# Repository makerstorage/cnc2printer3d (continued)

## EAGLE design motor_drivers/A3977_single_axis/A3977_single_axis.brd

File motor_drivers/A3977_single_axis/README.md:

A3977 Single Stepper Motor Driver Board

For more details, check out the product pages at

http://makerstorage.com/index.php?id_product=16&controller=product

MakerStorage invests time and resources providing this open source design, please support MakerStorage and open-source hardware by purchasing products from MakerStorage!

Designed by MakerStorage LLC.

Creative Commons Attribution, Share-Alike license, check https://creativecommons.org/licenses/by-sa/3.0/ for more information All text above must be included in any redistribution

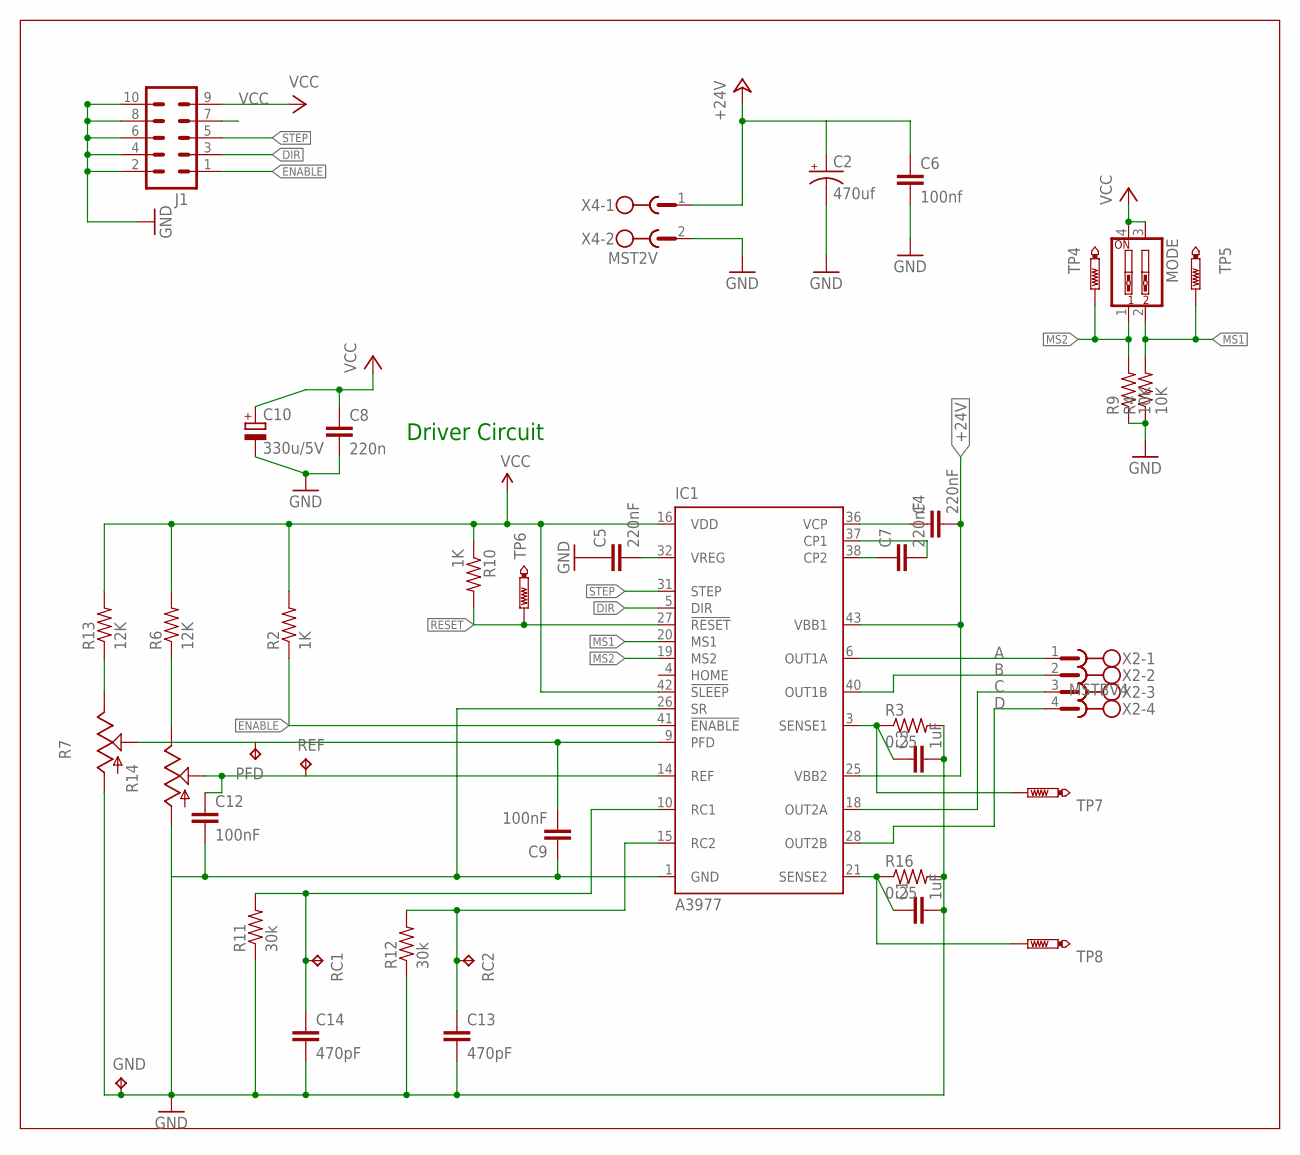
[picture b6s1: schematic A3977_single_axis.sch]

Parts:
C1, C3: 1uF; 0805
C2: 470uf; NIC_10X10.5_CAP
C4, C5, C7: 220nF; 0805
C6: 100nf; C1206
C8: 220n; C0805
C9, C12: 100nF; 0805
C10: 330u/5V; PANASONIC_F
C13, C14: 470pF; 0805
GND: TPPAD1-13; P1-13
IC1: A3977; PLCC44
J1: M05X2SHD; 2X5-SHROUDED
MODE: SW_DIP-2; EDG-02
PFD: TPPAD1-13; P1-13
R2, R10: 1K; 0805
R3, R16: 0.25; R2512
R4, R9: 10K; 0805
R6, R13: 12K; 0805
R7, R14: TRIM_US-CA6V; CA6V
R11, R12: 30k; 0805
RC1, RC2: TPPAD1-13; P1-13
REF: TPPAD1-13; P1-13
TP4, TP5, TP6, TP7, TP8: PTR1TP09R; TP09R
X2: MSTBV4
X4: MST2V; MSTBV2

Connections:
+24V: C2.+, C4.2, C6.1, IC1.25 (VBB2), IC1.43 (VBB1), X4.1
A: IC1.6 (OUT1A), X2.1
B: IC1.40 (OUT1B), X2.2
C: IC1.18 (OUT2A), X2.3
D: IC1.28 (OUT2B), X2.4
DIR: IC1.5 (DIR), J1.3
ENABLE: IC1.41 (!ENABLE), J1.1, R2.1
GND: C1.2, C2.-, C3.2, C5.1, C6.2, C8.2, C9.1, C10.-, C12.2, C13.2, C14.2, GND.TP, IC1.1 (GND), IC1.2 (GND), IC1.11 (GND), IC1.12 (GND), IC1.13 (GND), IC1.22 (GND), IC1.23 (GND), IC1.24 (GND), IC1.26 (SR), IC1.33 (GND), IC1.34 (GND), IC1.35 (GND), IC1.44 (GND), J1.2, J1.4, J1.6, J1.8, J1.10, R3.2, R4.1, R7.A, R9.1, R11.1, R12.1, R14.A, R16.2, X4.2
MS1: IC1.20 (MS1), MODE.2, R4.2, TP5.TP
MS2: IC1.19 (MS2), MODE.1, R9.2, TP4.TP
unnamed: C3.1, IC1.3 (SENSE1), R3.1, TP7.TP
unnamed: C1.1, IC1.21 (SENSE2), R16.1, TP8.TP
unnamed: C9.2, IC1.9 (PFD), PFD.TP, R7.S
unnamed: C14.1, IC1.10 (RC1), R11.2, RC1.TP
unnamed: C13.1, IC1.15 (RC2), R12.2, RC2.TP
unnamed: R6.1, R14.E
unnamed: C5.2, IC1.32 (VREG)
unnamed: R7.E, R13.1
unnamed: C7.1, IC1.38 (CP2)
unnamed: C12.1, IC1.14 (REF), R14.S, REF.TP
unnamed: C7.2, IC1.37 (CP1)
unnamed: C4.1, IC1.36 (VCP)
RESET: IC1.27 (!RESET), R10.2, TP6.TP
STEP: IC1.31 (STEP), J1.5
VCC: C8.1, C10.+, IC1.16 (VDD), IC1.42 (!SLEEP), J1.9, MODE.3, MODE.4, R2.2, R6.2, R10.1, R13.2

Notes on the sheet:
Driver Circuit

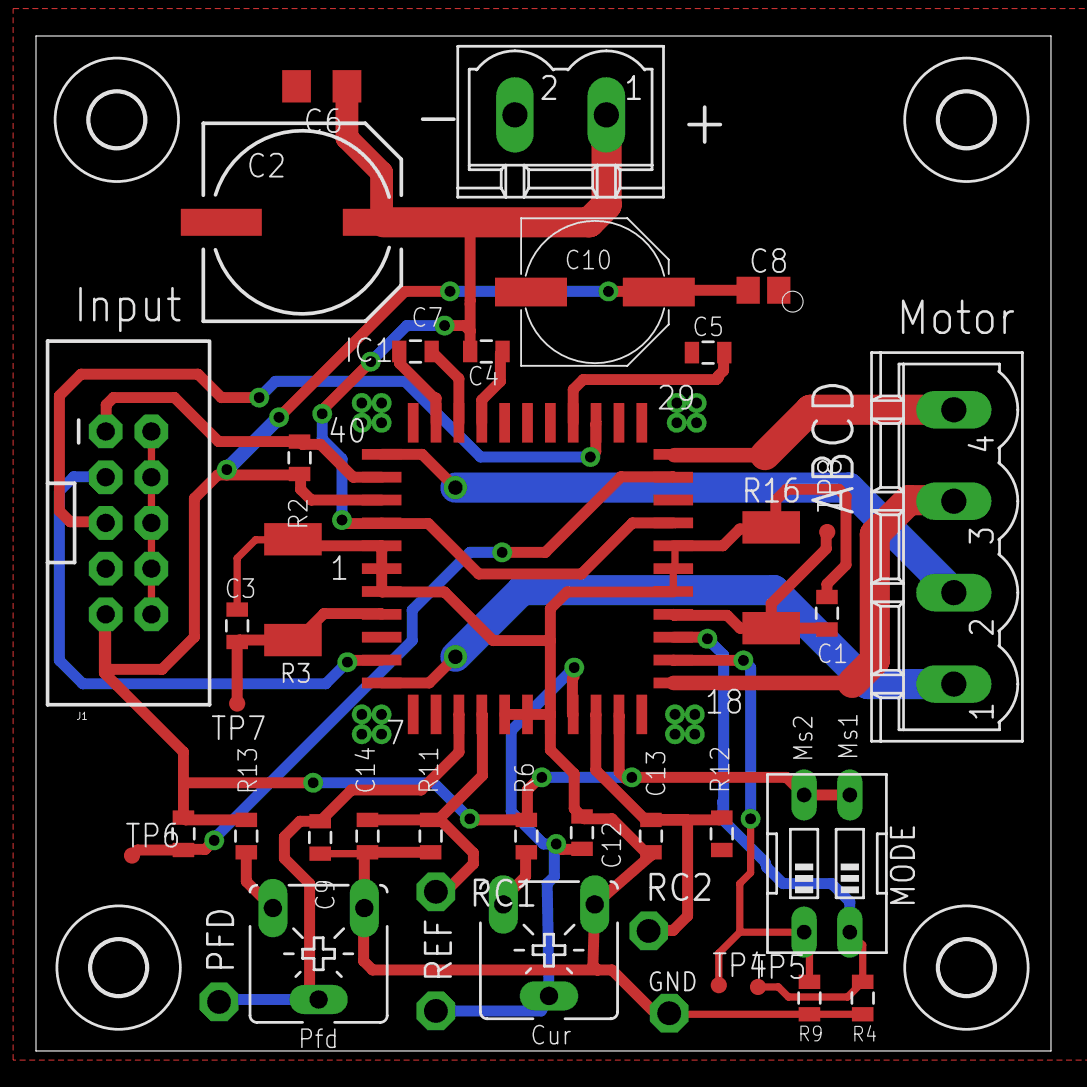
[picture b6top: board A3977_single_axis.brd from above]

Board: 2 copper layers, 56.4 x 56.4 mm, 44 parts (0 on the bottom side), 25 nets.

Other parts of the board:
U$1, U$2, U$3, U$4: 3,0

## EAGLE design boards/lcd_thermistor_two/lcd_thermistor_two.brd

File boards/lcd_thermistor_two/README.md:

LCD Thermistor Two Channel Extruder Controller (gecs2ts1)

For more details, check out the product pages at

https://cnc2printer3d.wordpress.com/gecs2ts1/

MakerStorage invests time and resources providing this open source design, please support MakerStorage and open-source hardware by purchasing products from MakerStorage!

Designed by MakerStorage LLC.

Creative Commons Attribution, Share-Alike license, check https://creativecommons.org/licenses/by-sa/3.0/ for more information All text above must be included in any redistribution

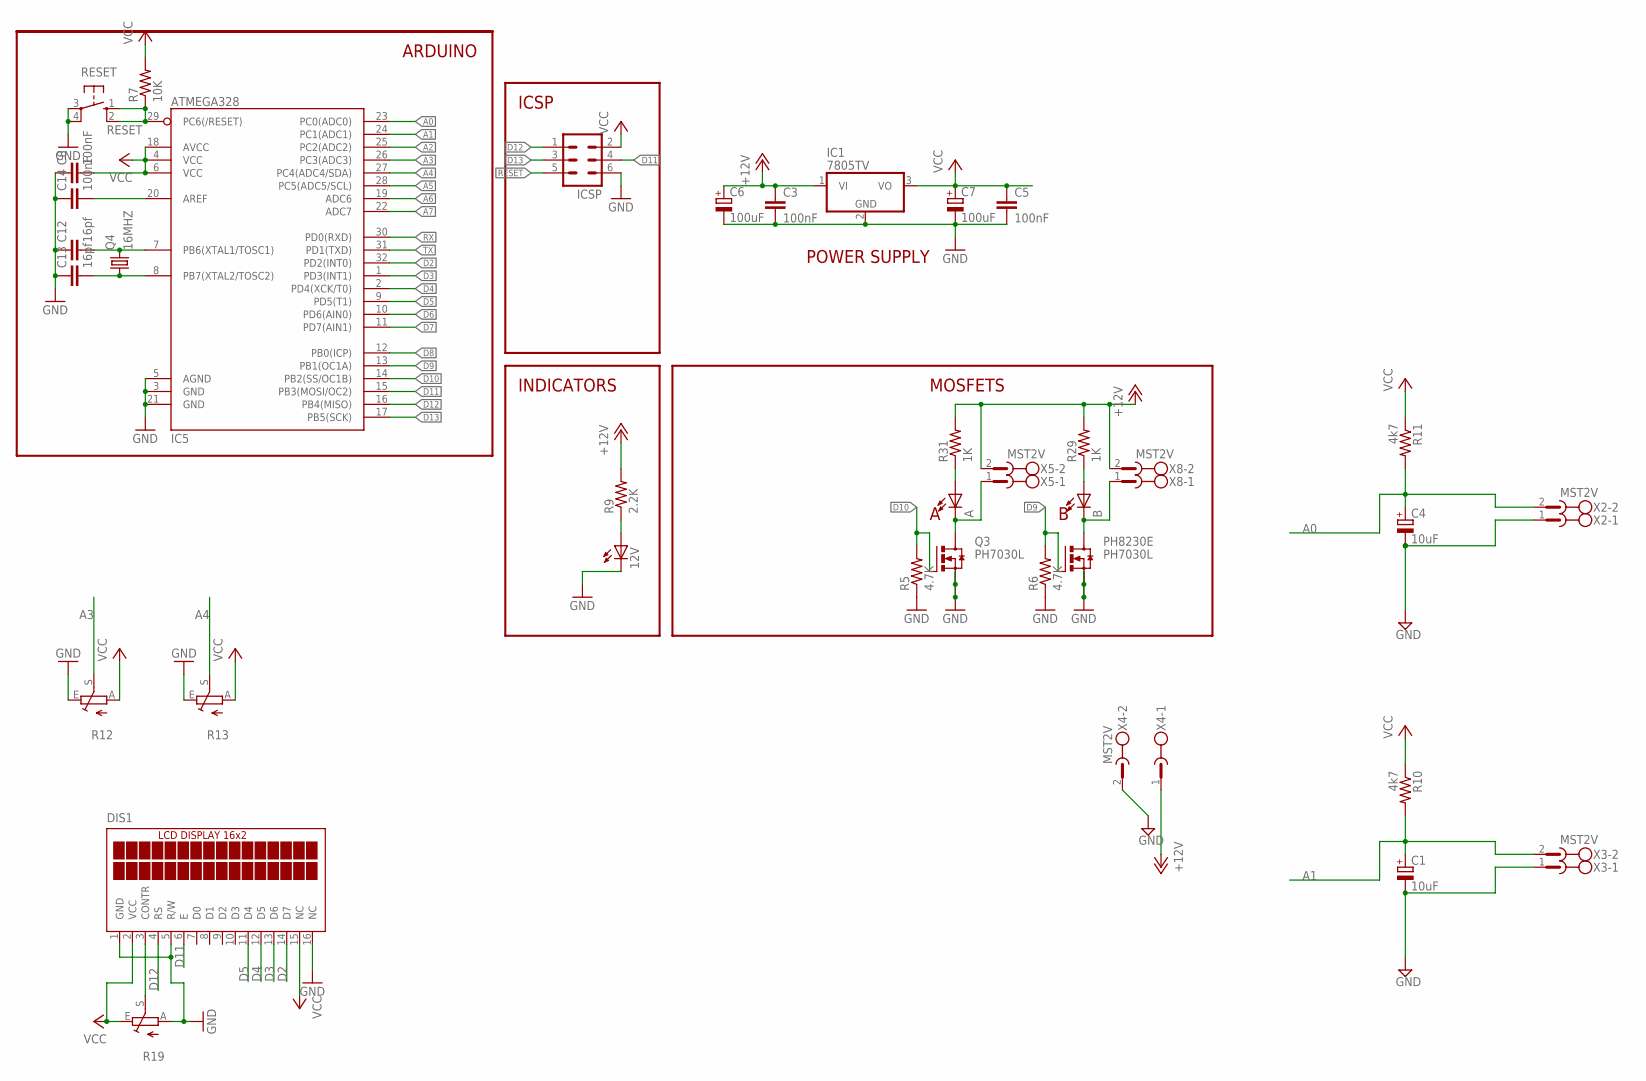
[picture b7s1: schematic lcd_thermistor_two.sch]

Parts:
12V: LED0805; LED-0805
A: LED0805; LED-0805
B: LED0805; LED-0805
C1, C4: 10uF; E5-6
C3, C5, C8, C14: 100nF; 0805
C6, C7: 100uF; E3,5-8
C12, C13: 16pf; 0805
DIS1: TUXGR_16X2_R2
IC1: 7805TV; TO220V
IC5: ATMEGA328; TQFP32-08
ICSP: ML6
PH8230E: PH7030L; SOT669
Q3: PH7030L; SOT669
Q4: 16MHZ; HC49/S
R5, R6: 4.7K; 0805
R7: 10K; 0805
R9: 2.2K; 0805
R10, R11: 4k7; 0805
R12, R13: TRIM_EU-B25U; B25U
R19: TRIM_EU-B25P; B25P
R29, R31: 1K; 0805
RESET: 10-XX; B3F-10XX
X2, X3, X4, X5, X8: MST2V; MSTBV2

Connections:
+12V: C3.1, C6.+, IC1.1 (VI), R9.2, R29.2, R31.2, X4.1, X5.2, X8.2
A0: C4.+, IC5.23 (PC0(ADC0)), R11.2, X2.2
A1: C1.+, IC5.24 (PC1(ADC1)), R10.2, X3.2
A2: IC5.25 (PC2(ADC2))
A3: IC5.26 (PC3(ADC3)), R12.S
A4: IC5.27 (PC4(ADC4/SDA)), R13.S
A5: IC5.28 (PC5(ADC5/SCL))
A6: IC5.19 (ADC6)
A7: IC5.22 (ADC7)
APWR: A.C, Q3.MB (D), X5.1
BPWR: B.C, PH8230E.MB (D), X8.1
D2: DIS1.14 (D7), IC5.32 (PD2(INT0))
D3: DIS1.13 (D6), IC5.1 (PD3(INT1))
D4: DIS1.12 (D5), IC5.2 (PD4(XCK/T0))
D5: DIS1.11 (D4), IC5.9 (PD5(T1))
D6: IC5.10 (PD6(AIN0))
D7: IC5.11 (PD7(AIN1))
D8: IC5.12 (PB0(ICP))
D9: IC5.13 (PB1(OC1A)), PH8230E.4 (G), R6.2
D10: IC5.14 (PB2(SS/OC1B)), Q3.4 (G), R5.2
D11: DIS1.6 (E), IC5.15 (PB3(MOSI/OC2)), ICSP.4
D12: DIS1.4 (RS), IC5.16 (PB4(MISO)), ICSP.1
D13: IC5.17 (PB5(SCK)), ICSP.3
GND: 12V.C, C1.-, C3.2, C4.-, C5.2, C6.-, C7.-, C8.1, C12.1, C13.1, C14.1, DIS1.1 (GND), DIS1.5 (R/W), DIS1.16 (NC), IC1.2 (GND), IC5.3 (GND), IC5.5 (AGND), IC5.21 (GND), ICSP.6, PH8230E.1 (S), PH8230E.2 (S), PH8230E.3 (S), Q3.1 (S), Q3.2 (S), Q3.3 (S), R5.1, R6.1, R12.E, R13.E, R19.A, RESET.3, RESET.4 (P1), X2.1, X3.1, X4.2
unnamed: C14.2, IC5.20 (AREF)
unnamed: 12V.A, R9.1
unnamed: DIS1.3 (CONTR), R19.S
unnamed: C12.2, IC5.7 (PB6(XTAL1/TOSC1)), Q4.2
unnamed: C13.2, IC5.8 (PB7(XTAL2/TOSC2)), Q4.1
unnamed: A.A, R31.1
unnamed: B.A, R29.1
RESET: IC5.29 (PC6(/RESET)), ICSP.5, R7.1, RESET.1 (S), RESET.2 (S1)
RX: IC5.30 (PD0(RXD))
TX: IC5.31 (PD1(TXD))
VCC: C5.1, C7.+, C8.2, DIS1.2 (VCC), DIS1.15 (NC), IC1.3 (VO), IC5.4 (VCC), IC5.6 (VCC), IC5.18 (AVCC), ICSP.2, R7.2, R10.1, R11.1, R12.A, R13.A, R19.E

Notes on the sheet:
MOSFETS
ICSP
ARDUINO
INDICATORS
POWER SUPPLY

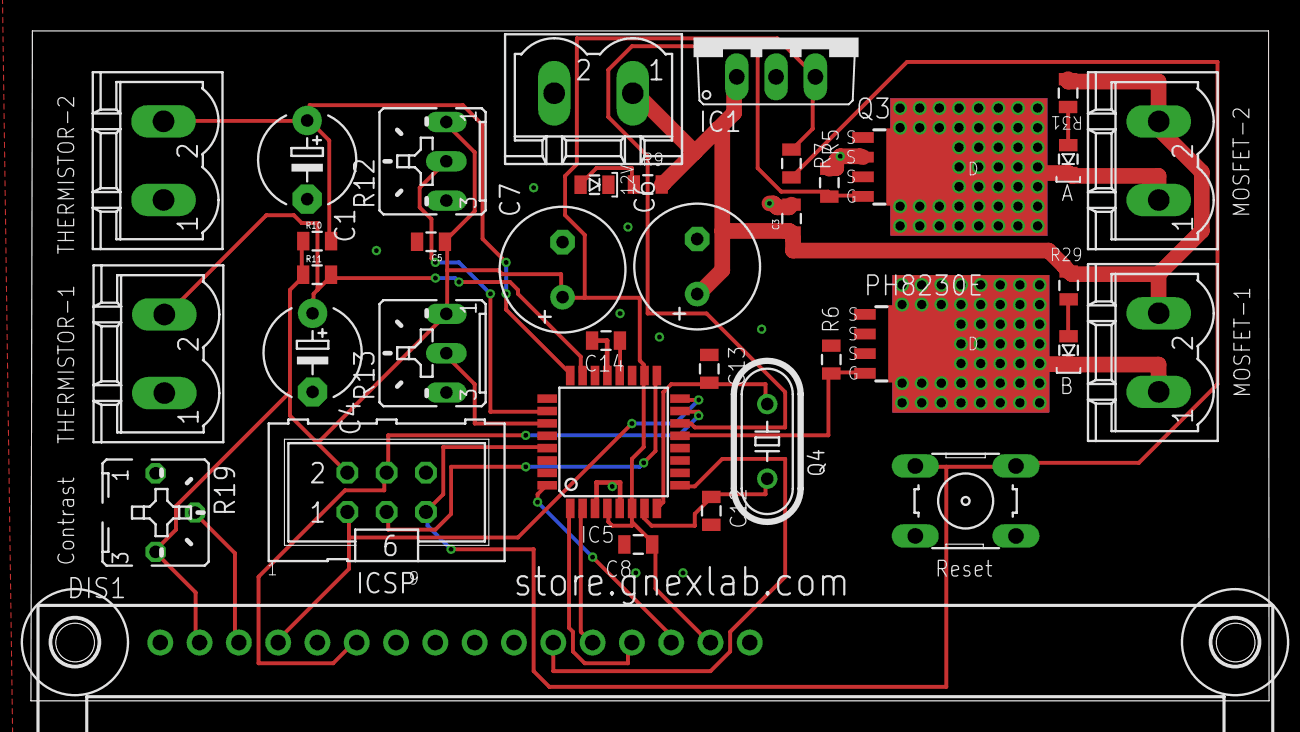
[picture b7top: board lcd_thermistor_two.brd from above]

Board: 2 copper layers, 80.0 x 43.3 mm, 39 parts (0 on the bottom side), 26 nets.

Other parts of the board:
U$1, U$4: 3,0

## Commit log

2016-05-05 2 commit
2016-05-08 cura profile added
2016-08-23 directories
2016-08-23 directories2
2016-08-23 directories3
2016-08-23 boards
2016-08-23 boards2
2016-08-23 boards3
2016-08-23 boards4
2016-08-23 boards5
2016-08-23 credits
2016-08-23 credits2
2016-08-23 credits3
2016-11-23 small read me update
2016-11-23 2 motor drivers added
2016-11-23 2 more drivers
2017-01-14 encoder to stepper board added
2017-01-14 digitalwritefast added
2018-08-23 new_seven_seg added
